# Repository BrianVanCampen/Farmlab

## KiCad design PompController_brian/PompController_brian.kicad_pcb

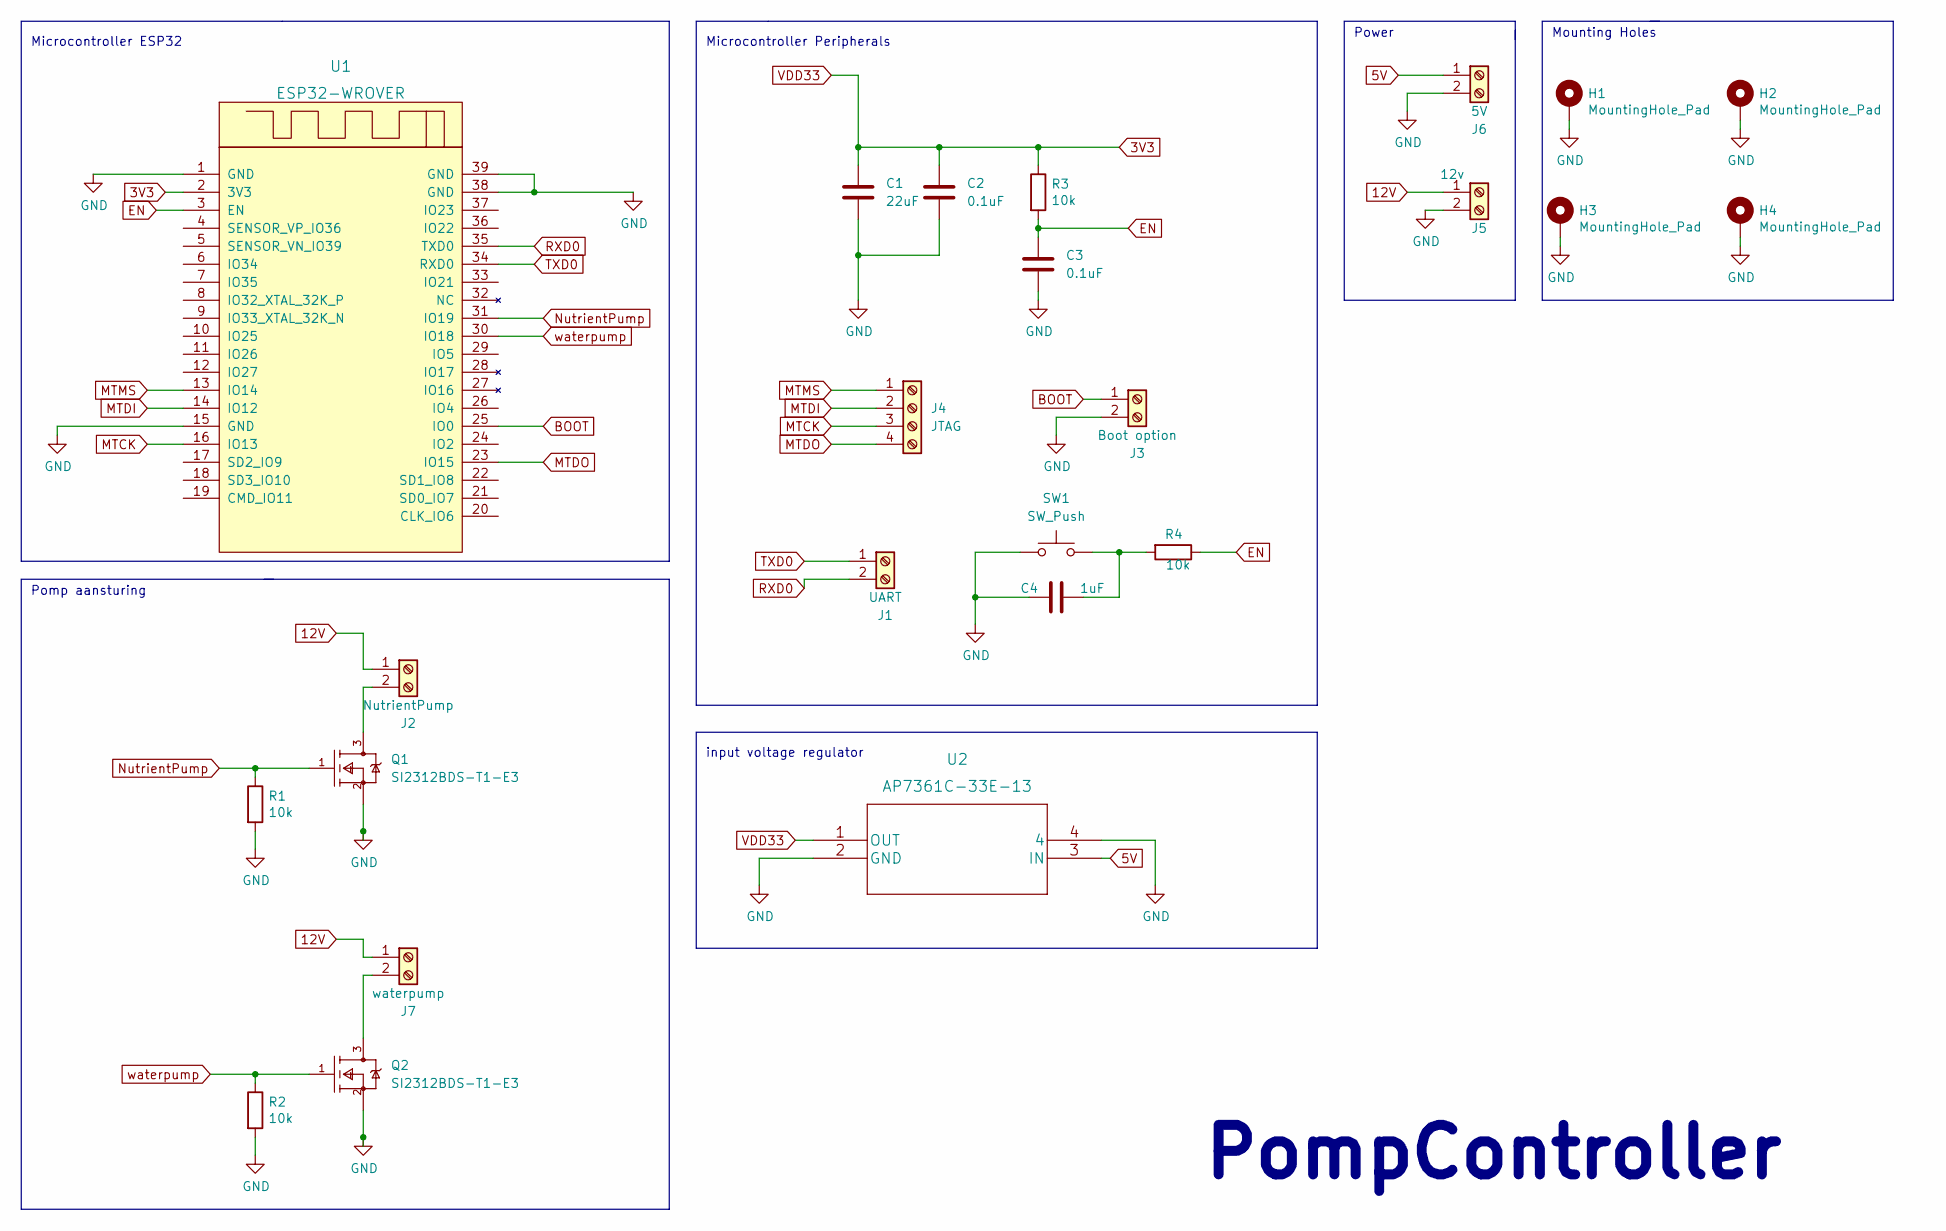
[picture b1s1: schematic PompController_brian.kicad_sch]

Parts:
C1: 22uF; C_0805_2012Metric
C2, C3: 0.1uF; C_0805_2012Metric
C4: 1uF; C_0805_2012Metric
H1, H2, H3, H4: MountingHole_Pad; MountingHole_3mm_Pad_Via
J1: UART; TerminalBlock_bornier-2_P5.08mm
J2: NutrientPump; TerminalBlock_bornier-2_P5.08mm
J3: Boot option; TerminalBlock_bornier-2_P5.08mm
J4: JTAG; TerminalBlock_bornier-4_P5.08mm
J5: 12v; TerminalBlock_bornier-2_P5.08mm
J6: 5V; TerminalBlock_bornier-2_P5.08mm
J7: waterpump; TerminalBlock_bornier-2_P5.08mm
Q1, Q2: SI2312BDS-T1-E3; Vishay-SI2312BDS-T1-E3-0; mouser part number 781-SI2312BDS-E3; digikey description MOSFET N-CH 20V 3.9A SOT23-3
R1, R2, R3, R4: 10k; R_0805_2012Metric
SW1: SW_Push; SW_Push_1P1T_NO_CK_KMR2
U1: ESP32-WROVER
U2: AP7361C-33E-13; SOT230P700X180-4N

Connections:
3V3: C1.2, C2.1, R3.1, U1.2 (3V3), U2.1 (OUT)
5V: J6.1, U2.3 (IN)
12V: J2.1, J5.1, J7.1
BOOT: J3.1, U1.25 (IO0)
EN: C3.1, R3.2, R4.1, U1.3 (EN)
GND: C1.1, C2.2, C3.2, C4.1, H1.1, H2.1, H3.1, H4.1, J3.2, J5.2, J6.2, Q1.2 (S), Q2.2 (S), R1.2, R2.2, SW1.1, U1.1 (GND), U1.15 (GND), U1.38 (GND), U1.39 (GND), U2.2 (GND), U2.4
MTCK: J4.3, U1.16 (IO13)
MTDI: J4.2, U1.14 (IO12)
MTDO: J4.4, U1.23 (IO15)
MTMS: J4.1, U1.13 (IO14)
unnamed: C4.2, R4.2, SW1.2
unnamed: J2.2, Q1.3 (D)
unnamed: J7.2, Q2.3 (D)
NutrientPump: Q1.1 (G), R1.1, U1.31 (IO19)
RXD0: J1.2, U1.35 (TXD0)
TXD0: J1.1, U1.34 (RXD0)
waterpump: Q2.1 (G), R2.1, U1.30 (IO18)

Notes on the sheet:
PompController
Microcontroller Peripherals
Microcontroller ESP32
Mounting Holes
Pomp aansturing
Power
input voltage regulator

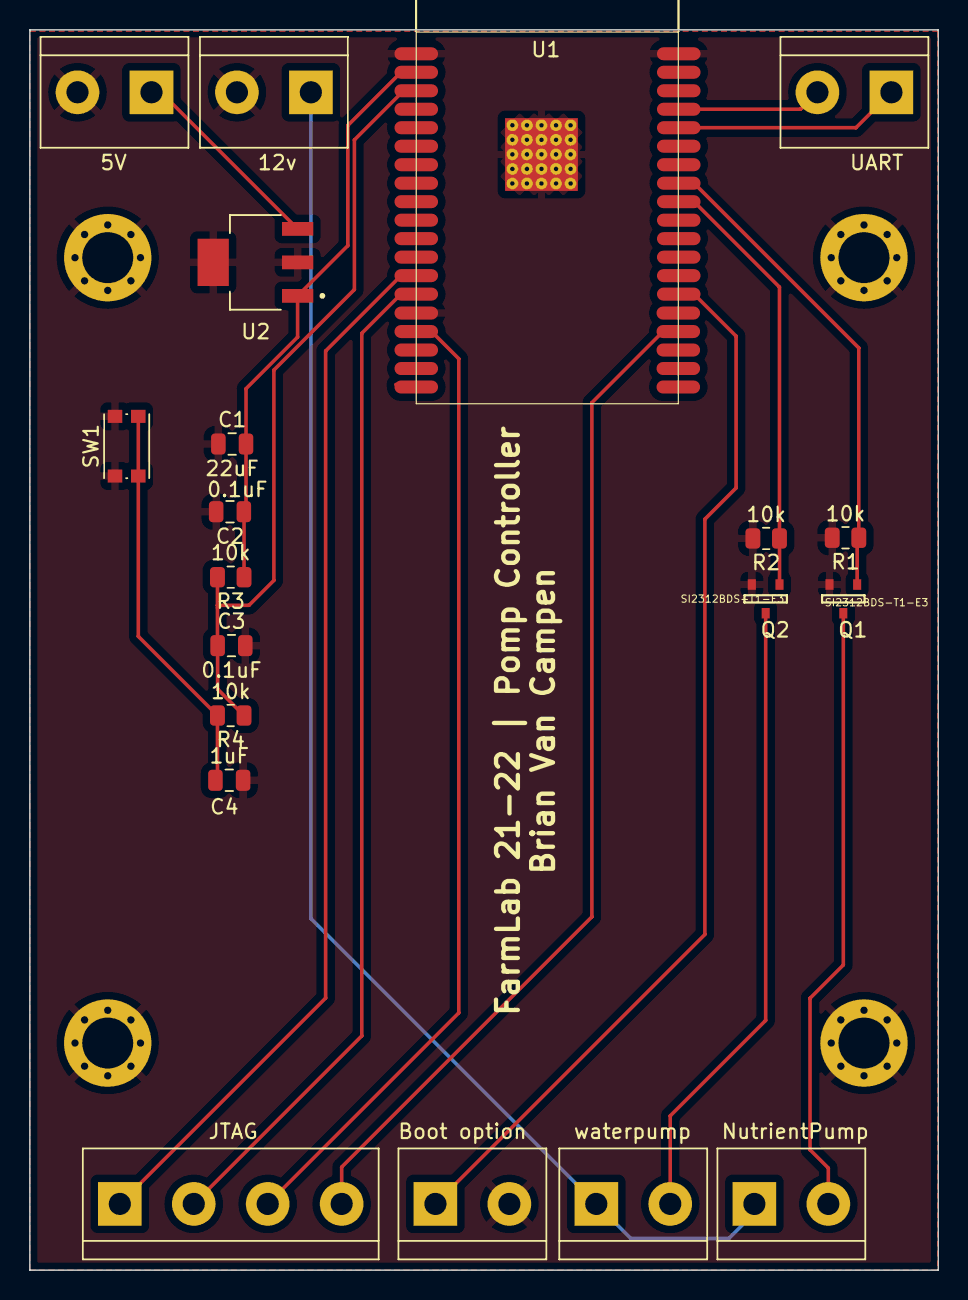
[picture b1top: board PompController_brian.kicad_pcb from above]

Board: 2 copper layers, 62.4 x 85.2 mm, 24 parts (0 on the bottom side), 17 nets.

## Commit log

2022-04-27 pompcontroller
2022-04-27 pomop
2022-05-04 update 3d ontwerp
2022-06-14 software analyse
2022-06-14 Rename pompcontroller.md to Documentatie_PompController.md
2022-06-14 update NODE-red
2022-06-15 update
    Handleiding software toegevoegd en problemen
